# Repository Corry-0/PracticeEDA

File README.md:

# PracticeEDA — 数字电路设计与仿真

C++17 / wxWidgets 桌面数字电路编辑器，当前版本 0.5，提供七类数字元件库。启动即进入数字电路设计界面。

个人发布仓库：[Corry-0/PracticeEDA](https://github.com/Corry-0/PracticeEDA)。

支持画布拖拽、60 种元件/注释、元件旋转、参数化逻辑门与选择器、1–32 位总线和任意位分组、独立时钟、可配置 RAM/ROM、子电路实例实时调试、自定义元件及跨工程复用、组合逻辑化简与自动生成电路、网表导出与 `.circ` 导入、项目保存加载、自动保存与崩溃恢复、PNG/打印、撤销重做、剪贴板与错误定位。

工具栏、分类树和常用元件栏已加入图标，复用了 `wxWidgets/samples` 中的资源，并补充数字逻辑符号。所有图标内嵌程序，支持高 DPI 缩放。

## AI 数字电路助手

Windows Release 编辑器的画布右上方有 **AI 助手**。打开 **模型设置**，选择 DeepSeek 或 OpenAI，再选择模型。可输入仅本次运行使用的 API Key，也可设置对应环境变量后重新启动软件。点击 **保存并测试** 会向选中的服务发送一次不含工程内容的工具调用测试。

| 服务商 | 聊天端点 | 密钥环境变量 |
|---|---|---|
| DeepSeek | `https://api.deepseek.com/chat/completions` | `DEEPSEEK_API_KEY` |
| OpenAI | `https://api.openai.com/v1/chat/completions` | `OPENAI_API_KEY` |
| 自定义 | 用户填写的完整 HTTPS Chat Completions 端点 | `PRACTICEEDA_AI_API_KEY` |

打开半加器并选中进位线，输入“这根线连接哪些端口？”。助手按需发送当前视图的元件、网络和仿真数据，可点击返回的对象 ID 定位。输入“生成一个半加器，输出 Sum 和 Carry”可预览新子电路及目标真值表。局部修复支持单驱动组合电路，整理导线需先选中目标。点击 **应用候选** 会形成一次可撤销的编辑。时序实例支持运行态查询。已画好的电路可选中导线或元件，按 Ctrl+Shift+R 重排关联导线，让跨线断口避开折点。

## 运行

直接启动 `build/Debug/PracticeEDA.exe`、`build/Release/PracticeEDA.exe` 或分发包 `dist/PracticeEDA/PracticeEDA.exe`。也可双击 `DigitalLogic.cmd`。旧的 `--logic` 启动参数仍可使用。

文件 → 打开半加器示例，可验证输入、逻辑门和真值表。更多示例：

- `examples/half-adder.logic.json`：半加器。
- `examples/bus-register.logic.json`：8 位总线、时钟和寄存器。
- `examples/hierarchical-adder.logic.json`：子电路封装与调用。
- `examples/defense-hierarchy.logic.json`：多层左右实例，独立寄存器与 RAM，可从模板创建。
- `examples/half-adder-physical.*`：实体芯片映射、标准网表及配套未布线 KiCad 板。
- `examples/circ-limited.circ`：外部电路 2.7 受限导入示例，含逻辑门、复用器、寄存器和未支持元件。
- `examples/drawn-half-adder.component.json`：带自定义符号外观的可运行半加器。
- `examples/half-adder.component.json`：可通过“文件 → 导入 → 自定义元件”复用的半加器。

工程使用 `.logic.json`，独立元件使用 `.component.json`；格式仍为 version 1，旧示例可读取。支持 Logisim 2.7.1 `.circ` 的[导入](docs/CIRC_IMPORT_CN.md)，无法映射的对象保留文字诊断。真值表支持最多 10 位输入，卡诺图支持最多 4 个变量；化简搜索达到预算时提供等价结果并注明未证明最少项。

## 新增功能

- **案例 → 实验案例**：提供半加器、全加器、8 位总线寄存器、4 位计数器、RAM 读写、层次化半加器，以及用独立 D 触发器搭成的 4 位并联寄存器、4 位串联移位寄存器。打开可编辑副本后，可对照说明查看预期结果。Ctrl+S 可另存工程。
- **帮助 → 操作指南**：原画布旁的七条操作提示迁入独立窗口；保留“数字逻辑使用说明”。
- **真实实例调试**：双击子电路进入所点击的运行实例，面包屑与“返回上级”保留父工程的时间、寄存器及 RAM；“编辑定义（复位）”单独进入可修改模式。
- **元件与存储配置**：门输入数及逐脚反相、选择位数、总线位段、零/符号扩展、时钟高低节拍和相位、下降沿触发、模计数与装载、RAM/ROM 地址容量均可设置；存储器有十六进制初值编辑和实例运行内存查看。
- **时钟与波形**：选中 Clock 后可输入频率和占空比，预览按工程时间分辨率换算的实际值。首次运行或单步推进时序电路时自动打开波形窗，支持多路信号、双游标测量和独立播放速度。详见 [时钟频率与时序波形](docs/DIGITAL_LOGIC_CN.md#时钟频率与时序波形)。
- **组合分析闭环**：真值表输出可编辑为 0、1、设计不关心项；展示化简式、格雷码卡诺图和圈组，生成与/或/非或仅 NAND 的新子电路，并重新仿真逐行验证。
- **调试与交付**：按输出信号选择连续 CSV 日志；最近工程、空白/半加器模板、右键菜单、可选比例 PNG、全部定义批量 PNG。
- **文件操作分组**：“文件 → 导入”集中提供 `.circ`、自定义元件和真值表 CSV；“文件 → 导出”集中提供完整/批量 PNG、最近分析 CSV、逻辑网表 JSON、KiCad PCB 及自定义元件。顶部工具栏从左到右为新建/打开/保存、相邻的导入/导出下拉按钮、选择/导线及常用元件。

- **画布与属性交互**：全部内置元件采用边框端子，移除外伸引线；元件库图标、画布、放置预览和导出共用绘制。输入输出使用 28×28 主体和五种实时状态色；放置一次后自动回到选择模式，靠近引脚仍可直接布线。
- **局部智能布线**：新建导线按引脚方向出线并绕开主体，不同网络保持走线间距；移动或新放元件后只调整受影响的导线。支持 `Ctrl+Shift+R` 重排选中导线、选中后拖动线段、`Alt+单击` / `Tab` 切换重叠候选，以及交叉断口。打开旧工程保持原布局，纯走线调整保留仿真状态。详见 [布线说明](docs/ROUTING_CN.md)。
- **左侧工作区**：实例层次按内容收缩，元件库下方为可调高度的“属性 / 值”表格；支持方向下拉、逐输入反相和放置前的工具参数。子电路选择框旁的加号和删除按钮分别对应 `Ctrl+Shift+N`、`Ctrl+Shift+Delete`，主电路和被引用的定义受删除保护。
- **画布 ERC 提示**：取消固定诊断面板和聚合气泡；每个问题对象外围显示一枚小图标，红色圆形叉号表示错误，黄色三角感叹号表示警告，同时保留对象颜色提示。图标自动避让主体、标签、引脚和导线，悬停查看规则及修复建议，点击打开该对象的问题列表；单击列表项缩放定位并高亮。也可用 `Ctrl+Shift+E` 打开列表；不显示迷你地图热点。现有规则覆盖范围见 [ERC 自查报告](docs/audits/2026-10-22-erc/自查报告.md)。

- **图形工具与元件外观**：直线、曲线、矩形、椭圆、圆，支持线宽、填充、控制点调整、复制及撤销。选择“工具 → 编辑元件外观”设计实例符号，选择“工具 → 返回电路编辑”继续内部逻辑。详见[操作说明](docs/CUSTOM_COMPONENTS_NETLIST_CN.md#图形与元件外观)。

- **文件 → 导入 → Logisim 2.7 电路**：导入支持范围内的元件、参数、连线和层次实例。导入后使用 `.logic.json` 保存，详见 [中文导入说明](docs/CIRC_IMPORT_CN.md)。“文件 → 打开”和命令行仍可读取 `.circ`。

- **项目 → 新建自定义元件**：填写元件名称与输入/输出接口（如 `DATA:8`），然后在画布实现内部逻辑。切回 `main`，从“自定义元件 / 子电路”库放置实例；双击实例观察实际运行状态，修改结构请进入定义编辑。自定义符号接口坐标按稳定 ID 保存，可单独安排位置。
- **文件 → 导出 → 当前电路为自定义元件 / 文件 → 导入 → 自定义元件**：保存独立 `.component.json`，自动携带嵌套依赖。导入不会覆盖已有定义，重名自动添加后缀，支持撤销重做。
- **文件 → 导出 → 逻辑网表 JSON**：保存为 `circuit.json`，包含当前电路及嵌套实例的连接、位宽、器件参数、初值、存储器数据、网络标签和连接别名，供程序读取和分析。导出保留运行中的仿真状态；继续编辑设计请保存 `.logic.json` 工程。
- **文件 → 导出 → KiCad PCB**：将支持的单比特组合门映射为真实 74HC DIP 芯片，保存 `circuit.kicad_pcb`，同时生成 `circuit.net` 和 `circuit.mapping.json`。在 KiCad PCB 编辑器打开板文件继续布局和布线。实际加载及范围见 [PCB 交换说明](docs/PCB_EXCHANGE_CN.md)。

具体格式、使用边界与示例见 [自定义元件与网表说明](docs/CUSTOM_COMPONENTS_NETLIST_CN.md)。

## 构建和验证

需要 Visual Studio 2022 C++ 桌面开发工具、CMake 3.20+、MSVC x64 wxWidgets 3.2+。请先准备 wxWidgets 静态库，可放在仓库同级的 `wxWidgets/` 目录，或通过 `-WxRoot` 指定安装目录。构建产物与本地依赖不包含在源码仓库中。

```sh
git clone https://github.com/Corry-0/PracticeEDA.git
cd PracticeEDA
```

```powershell
.\scripts\build.ps1 -Configuration Debug -GuiTest
.\scripts\build.ps1 -Configuration Release -GuiTest -Package
```

Visual Studio 直接打开 `build/PracticeEDA.sln`，选择 Debug/x64 或 Release/x64，按 F5。核心测试也可脱离 GUI 构建：

```sh
cmake -S . -B build-core -DEDA_BUILD_GUI=OFF
cmake --build build-core --config Debug
ctest --test-dir build-core -C Debug --output-on-failure
```

## 结构

| 位置 | 内容 |
| --- | --- |
| `include/Digital.h`、`src/Digital.cpp` | 数字电路、仿真、子电路、文件格式、历史与分析 |
| `src/CircImport.cpp`、`tests/circ_import_tests.cpp` | 外部电路 2.7 XML 受限转换、原生校验复用及导入回归 |
| `include/LogicAnalysis.h`、`src/LogicAnalysis.cpp` | 布尔化简、卡诺图、CSV 分析表与电路生成/反向验证 |
| `include/PcbExport.h`、`src/PcbExport.cpp` | 受限真实芯片/封装映射，标准网表与配套 PCB |
| `src/CustomComponents.cpp` | 自定义接口创建、依赖打包、导入重命名与 ID 重映射 |
| `include/LogicSupport.h`、`src/LogicSupport.cpp` | 画布几何、导线基础类型、文件读写 |
| `include/WxSupport.h` | wxWidgets 字符和路径转换 |
| `include/DigitalEditor.h`、`src/DigitalEditor.cpp` | 数字编辑器界面、交互与 GUI 检查 |
| `src/LogicEditorTools.cpp` | 初值/运行内存、引脚布局、持续日志及批量图片窗口 |
| `src/LogicDiagnostics.cpp` | ERC 颜色提示、外围警示图标避让、悬停详情与按需问题窗口 |
| `include/LogicRouting.h`、`src/LogicRouting.cpp` | 正交避障、不同网络间距、局部重排和交叉计算 |
| `src/LogicWireTools.cpp`、`tests/routing_tests.cpp` | 画布布线交互、线段拖动、候选切换和路由回归 |
| `include/LogicIcons.h`、`src/LogicIcons.cpp` | 内嵌示例资源、数字符号图标 |
| `src/App.cpp` | 唯一入口，直接创建数字编辑器 |
| `resources/wxwidgets/` | 从 wxWidgets samples 复制的原始图标数据 |
| `tests/digital_tests.cpp` | 数字逻辑及基础功能回归 |
| `tests/advanced_core_tests.cpp`、`tests/analysis_tests.cpp` | 参数化元件、双向开关/弱驱动、实例内存与组合分析闭环 |
| `tests/component_netlist_tests.cpp`、`tests/verify_netlists.py` | 自定义元件、仿真状态保护、网表结构与逐位连接比对 |

使用详情见 [数字逻辑使用说明](docs/DIGITAL_LOGIC_CN.md)，编译见 [Visual Studio 指南](docs/VISUAL_STUDIO_CN.md)，资源来源与许可见 [图标说明](resources/ICONS.md)。

源码维护入口见 [代码阅读指南](docs/CODE_GUIDE_CN.md)，本次验证记录见 [测试报告](docs/TEST_REPORT_CN.md)。

## 四人答辩材料

材料已按 2026-10-08 当前源码和实际 Debug / Release 回归同步，重点展示真实多层实例调试、组合综合与文件交换；25 页，常人元、闫浩楠、杨曙启、黄歆贻四人主讲，18 分钟讲解加 2 分钟机动。

- [材料入口与演示说明](docs/defense/00_阅读与演示说明.md)
- [源码详细讲解](docs/defense/01_源码详细讲解.md)
- [四人分工与排练](docs/defense/02_四人分工与排练.md)
- [逐页答辩讲稿](docs/defense/03_答辩逐页讲稿.md)
- [方案对比与迭代证据](docs/defense/04_方案对比与迭代证据.md)
- [当前进度与现场演示清单](docs/defense/05_当前进度与现场演示.md)
- [25 页网页展示文件](docs/defense/ppt/index.html)：下载或克隆后用浏览器打开，支持离线展示、交接页与演讲者备注。
- [可编辑 PPTX](docs/defense/ppt/PracticeEDA_四人答辩_2026-10-08_正式版.pptx)：同一内容源，25 页原生文字/表格，每页含备注。
- [整套材料 ZIP](docs/PracticeEDA_四人答辩材料.zip)

## 项目来源

本仓库保留 [LEVE1012/ElectronicComponent_Practice-](https://github.com/LEVE1012/ElectronicComponent_Practice-) 的原型提交历史，在此基础上整理和扩展为当前 PracticeEDA。历史提交作者与第三方资源署名保持原样；第三方许可文本见 `third_party/`，图标来源见 [资源说明](resources/ICONS.md)。

当前以数字逻辑为主，PCB 仅提供上述受限实体映射，板未布线；不含模拟电路求解和制造验收。分发包静态链接 wxWidgets，Windows 目标机器仍需 Microsoft Visual C++ x64 运行库。

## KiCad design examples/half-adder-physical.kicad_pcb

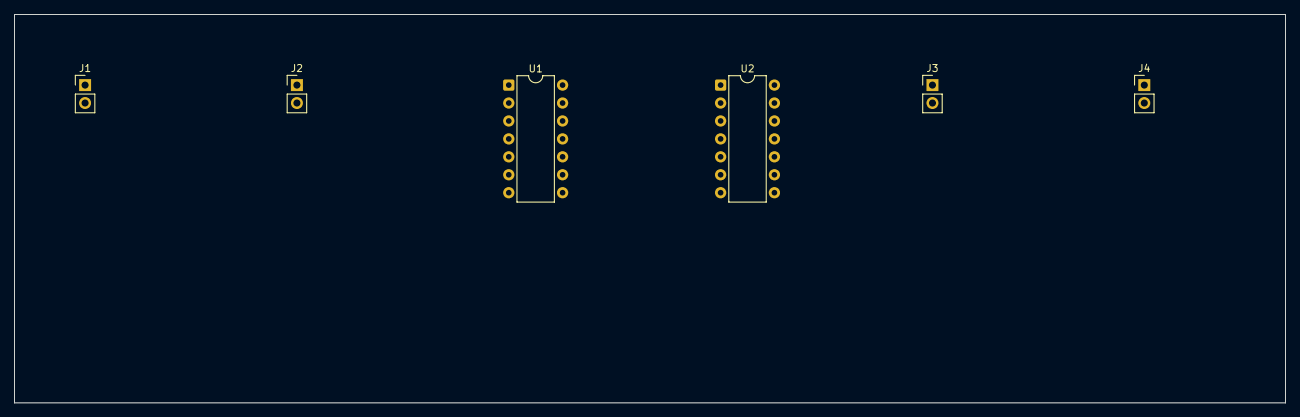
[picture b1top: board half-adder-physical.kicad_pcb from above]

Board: 2 copper layers, 180.0 x 55.0 mm, 6 parts (0 on the bottom side), 6 nets, no tracks yet.

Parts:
J1: A; PinHeader_1x02_P2.54mm_Vertical
J2: B; PinHeader_1x02_P2.54mm_Vertical
J3: Sum; PinHeader_1x02_P2.54mm_Vertical
J4: Carry; PinHeader_1x02_P2.54mm_Vertical
U1: 74HC86; DIP-14_W7.62mm
U2: 74HC08; DIP-14_W7.62mm

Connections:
GND: J1.2, J2.2, J3.2, J4.2, U1.4, U1.5, U1.7, U1.9, U1.10, U1.12, U1.13, U2.4, U2.5, U2.7, U2.9, U2.10, U2.12, U2.13
N1: J1.1, U1.1, U2.1
N2: J2.1, U1.2, U2.2
N3: J3.1, U1.3
N4: J4.1, U2.3
VCC: U1.14, U2.14
